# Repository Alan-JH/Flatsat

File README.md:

# Flatsat
Plug and play flatsat testing board for PC104 stack boards

## mainboard
Custom designed main board, includes spaces for three PC104 boards and a passthrough in and passthrough out connector

5V, 3.3V, BATV, GND traces are widened to 0.762mm

## pc104-breakout
Breakout board for probing pc104 pins

## pc104-bridge
Bridge to connect between mainboards

pc104-breakout and pc104-bridge taken and adapted to kicad from https://github.com/JonisK/FlatSat

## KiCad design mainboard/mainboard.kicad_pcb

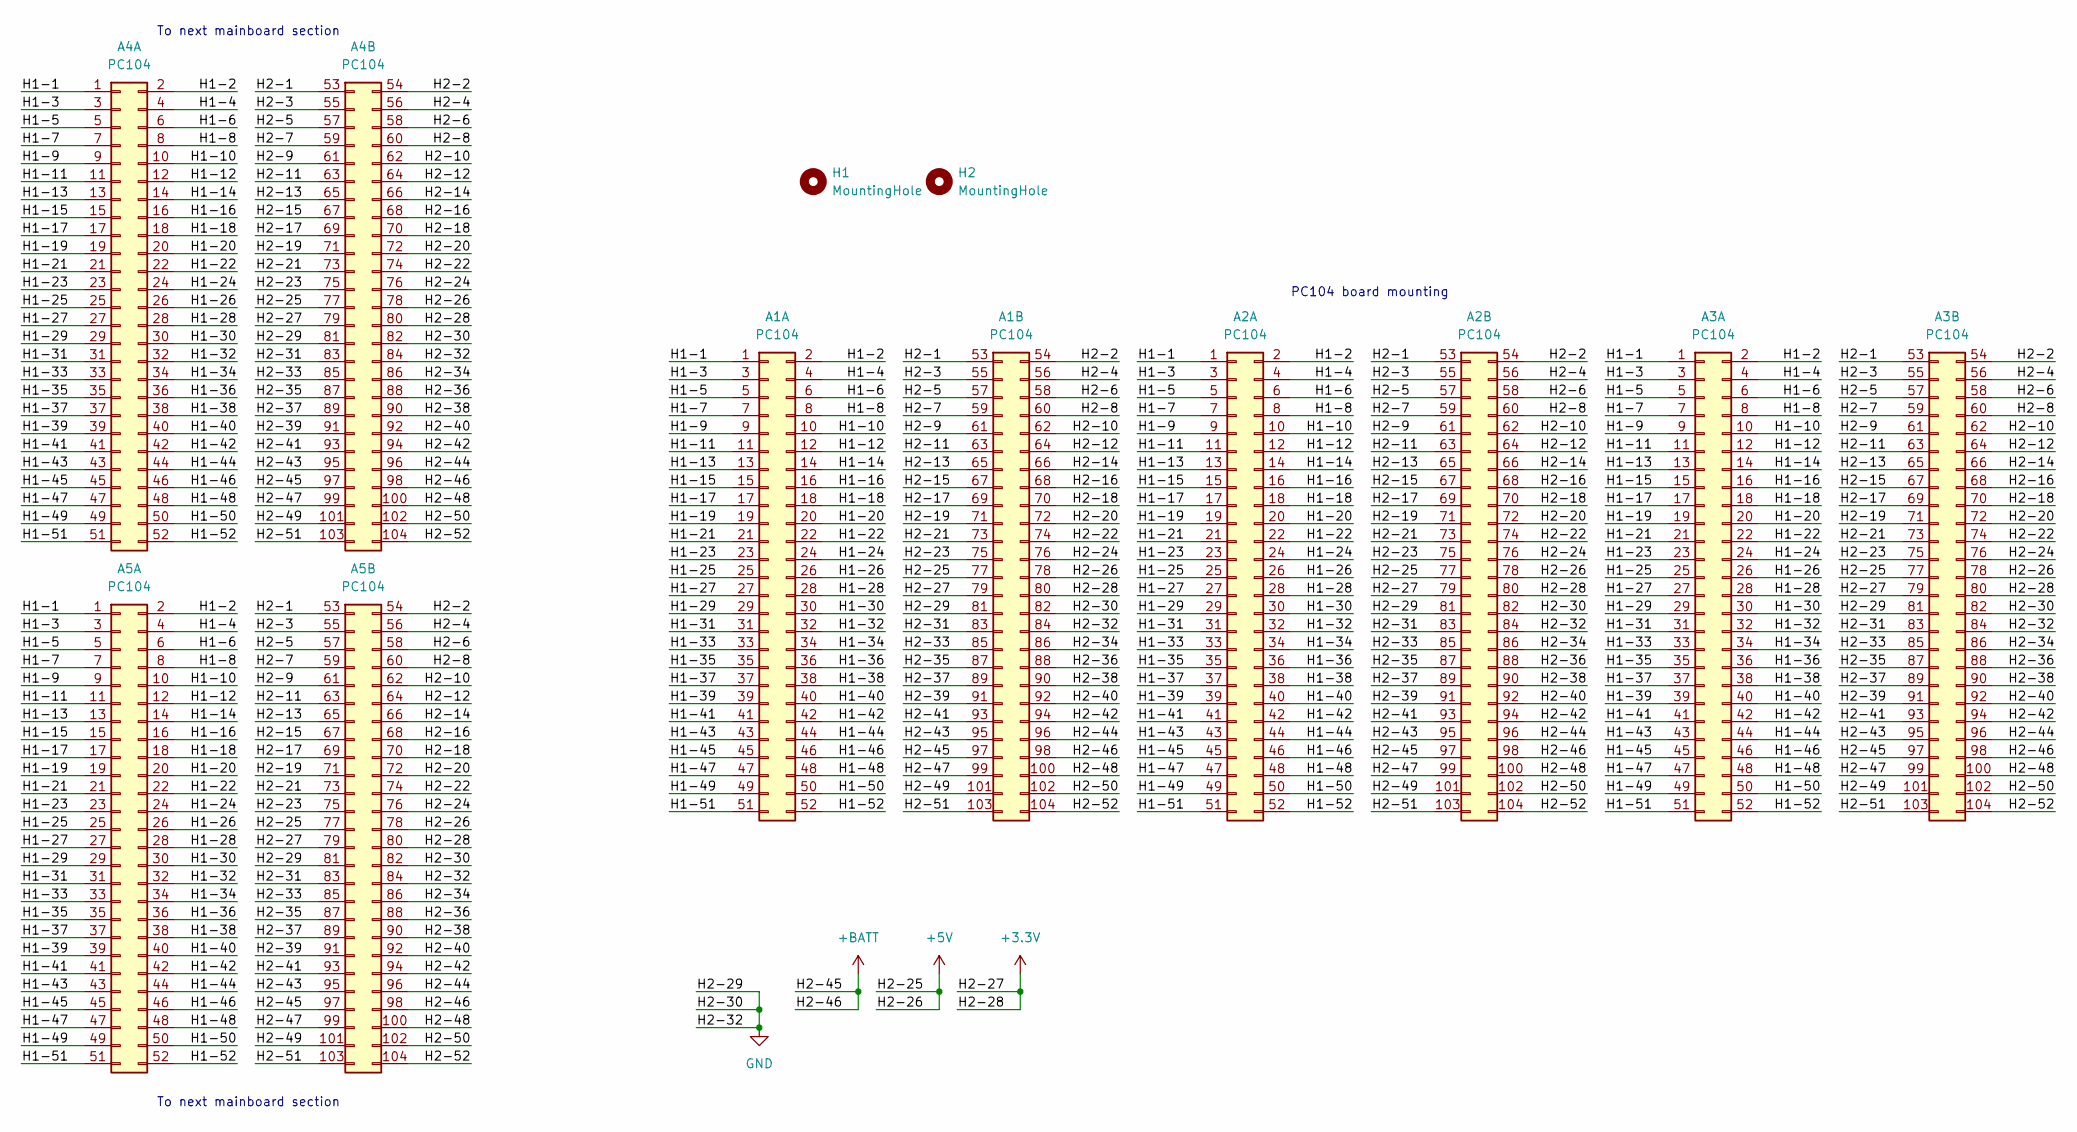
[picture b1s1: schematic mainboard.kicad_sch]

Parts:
A1, A2, A3: PC104
A4, A5: PC104; Header
H1, H2: MountingHole; MountingHole_3.2mm_M3

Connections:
+3V3: A1.79 (Pin_27), A1.80 (Pin_28), A2.79 (Pin_27), A2.80 (Pin_28), A3.79 (Pin_27), A3.80 (Pin_28), A4.79 (Pin_27), A4.80 (Pin_28), A5.79 (Pin_27), A5.80 (Pin_28)
+5V: A1.77 (Pin_25), A1.78 (Pin_26), A2.77 (Pin_25), A2.78 (Pin_26), A3.77 (Pin_25), A3.78 (Pin_26), A4.77 (Pin_25), A4.78 (Pin_26), A5.77 (Pin_25), A5.78 (Pin_26)
+BATT: A1.97 (Pin_45), A1.98 (Pin_46), A2.97 (Pin_45), A2.98 (Pin_46), A3.97 (Pin_45), A3.98 (Pin_46), A4.97 (Pin_45), A4.98 (Pin_46), A5.97 (Pin_45), A5.98 (Pin_46)
/H1-1: A1.1, A2.1, A3.1, A4.1, A5.1
/H1-2: A1.2, A2.2, A3.2, A4.2, A5.2
/H1-3: A1.3, A2.3, A3.3, A4.3, A5.3
/H1-4: A1.4, A2.4, A3.4, A4.4, A5.4
/H1-5: A1.5, A2.5, A3.5, A4.5, A5.5
/H1-6: A1.6, A2.6, A3.6, A4.6, A5.6
/H1-7: A1.7, A2.7, A3.7, A4.7, A5.7
/H1-8: A1.8, A2.8, A3.8, A4.8, A5.8
/H1-9: A1.9, A2.9, A3.9, A4.9, A5.9
/H1-10: A1.10, A2.10, A3.10, A4.10, A5.10
/H1-11: A1.11, A2.11, A3.11, A4.11, A5.11
/H1-12: A1.12, A2.12, A3.12, A4.12, A5.12
/H1-13: A1.13, A2.13, A3.13, A4.13, A5.13
/H1-14: A1.14, A2.14, A3.14, A4.14, A5.14
/H1-15: A1.15, A2.15, A3.15, A4.15, A5.15
/H1-16: A1.16, A2.16, A3.16, A4.16, A5.16
/H1-17: A1.17, A2.17, A3.17, A4.17, A5.17
/H1-18: A1.18, A2.18, A3.18, A4.18, A5.18
/H1-19: A1.19, A2.19, A3.19, A4.19, A5.19
/H1-20: A1.20, A2.20, A3.20, A4.20, A5.20
/H1-21: A1.21, A2.21, A3.21, A4.21, A5.21
/H1-22: A1.22, A2.22, A3.22, A4.22, A5.22
/H1-23: A1.23, A2.23, A3.23, A4.23, A5.23
/H1-24: A1.24, A2.24, A3.24, A4.24, A5.24
/H1-25: A1.25, A2.25, A3.25, A4.25, A5.25
/H1-26: A1.26, A2.26, A3.26, A4.26, A5.26
/H1-27: A1.27, A2.27, A3.27, A4.27, A5.27
/H1-28: A1.28, A2.28, A3.28, A4.28, A5.28
/H1-29: A1.29, A2.29, A3.29, A4.29, A5.29
/H1-30: A1.30, A2.30, A3.30, A4.30, A5.30
/H1-31: A1.31, A2.31, A3.31, A4.31, A5.31
/H1-32: A1.32, A2.32, A3.32, A4.32, A5.32
/H1-33: A1.33, A2.33, A3.33, A4.33, A5.33
/H1-34: A1.34, A2.34, A3.34, A4.34, A5.34
/H1-35: A1.35, A2.35, A3.35, A4.35, A5.35
/H1-36: A1.36, A2.36, A3.36, A4.36, A5.36
/H1-37: A1.37, A2.37, A3.37, A4.37, A5.37
/H1-38: A1.38, A2.38, A3.38, A4.38, A5.38
/H1-39: A1.39, A2.39, A3.39, A4.39, A5.39
/H1-40: A1.40, A2.40, A3.40, A4.40, A5.40
/H1-41: A1.41, A2.41, A3.41, A4.41, A5.41
/H1-42: A1.42, A2.42, A3.42, A4.42, A5.42
/H1-43: A1.43, A2.43, A3.43, A4.43, A5.43
/H1-44: A1.44, A2.44, A3.44, A4.44, A5.44
/H1-45: A1.45, A2.45, A3.45, A4.45, A5.45
/H1-46: A1.46, A2.46, A3.46, A4.46, A5.46
/H1-47: A1.47, A2.47, A3.47, A4.47, A5.47
/H1-48: A1.48, A2.48, A3.48, A4.48, A5.48
/H1-49: A1.49, A2.49, A3.49, A4.49, A5.49
/H1-50: A1.50, A2.50, A3.50, A4.50, A5.50
/H1-51: A1.51, A2.51, A3.51, A4.51, A5.51
/H1-52: A1.52, A2.52, A3.52, A4.52, A5.52
/H2-1: A1.53 (Pin_1), A2.53 (Pin_1), A3.53 (Pin_1), A4.53 (Pin_1), A5.53 (Pin_1)
/H2-2: A1.54 (Pin_2), A2.54 (Pin_2), A3.54 (Pin_2), A4.54 (Pin_2), A5.54 (Pin_2)
/H2-3: A1.55 (Pin_3), A2.55 (Pin_3), A3.55 (Pin_3), A4.55 (Pin_3), A5.55 (Pin_3)
/H2-4: A1.56 (Pin_4), A2.56 (Pin_4), A3.56 (Pin_4), A4.56 (Pin_4), A5.56 (Pin_4)
/H2-5: A1.57 (Pin_5), A2.57 (Pin_5), A3.57 (Pin_5), A4.57 (Pin_5), A5.57 (Pin_5)
/H2-6: A1.58 (Pin_6), A2.58 (Pin_6), A3.58 (Pin_6), A4.58 (Pin_6), A5.58 (Pin_6)
/H2-7: A1.59 (Pin_7), A2.59 (Pin_7), A3.59 (Pin_7), A4.59 (Pin_7), A5.59 (Pin_7)
/H2-8: A1.60 (Pin_8), A2.60 (Pin_8), A3.60 (Pin_8), A4.60 (Pin_8), A5.60 (Pin_8)
/H2-9: A1.61 (Pin_9), A2.61 (Pin_9), A3.61 (Pin_9), A4.61 (Pin_9), A5.61 (Pin_9)
/H2-10: A1.62 (Pin_10), A2.62 (Pin_10), A3.62 (Pin_10), A4.62 (Pin_10), A5.62 (Pin_10)
/H2-11: A1.63 (Pin_11), A2.63 (Pin_11), A3.63 (Pin_11), A4.63 (Pin_11), A5.63 (Pin_11)
/H2-12: A1.64 (Pin_12), A2.64 (Pin_12), A3.64 (Pin_12), A4.64 (Pin_12), A5.64 (Pin_12)
/H2-13: A1.65 (Pin_13), A2.65 (Pin_13), A3.65 (Pin_13), A4.65 (Pin_13), A5.65 (Pin_13)
/H2-14: A1.66 (Pin_14), A2.66 (Pin_14), A3.66 (Pin_14), A4.66 (Pin_14), A5.66 (Pin_14)
/H2-15: A1.67 (Pin_15), A2.67 (Pin_15), A3.67 (Pin_15), A4.67 (Pin_15), A5.67 (Pin_15)
/H2-16: A1.68 (Pin_16), A2.68 (Pin_16), A3.68 (Pin_16), A4.68 (Pin_16), A5.68 (Pin_16)
/H2-17: A1.69 (Pin_17), A2.69 (Pin_17), A3.69 (Pin_17), A4.69 (Pin_17), A5.69 (Pin_17)
/H2-18: A1.70 (Pin_18), A2.70 (Pin_18), A3.70 (Pin_18), A4.70 (Pin_18), A5.70 (Pin_18)
/H2-19: A1.71 (Pin_19), A2.71 (Pin_19), A3.71 (Pin_19), A4.71 (Pin_19), A5.71 (Pin_19)
/H2-20: A1.72 (Pin_20), A2.72 (Pin_20), A3.72 (Pin_20), A4.72 (Pin_20), A5.72 (Pin_20)
/H2-21: A1.73 (Pin_21), A2.73 (Pin_21), A3.73 (Pin_21), A4.73 (Pin_21), A5.73 (Pin_21)
/H2-22: A1.74 (Pin_22), A2.74 (Pin_22), A3.74 (Pin_22), A4.74 (Pin_22), A5.74 (Pin_22)
/H2-23: A1.75 (Pin_23), A2.75 (Pin_23), A3.75 (Pin_23), A4.75 (Pin_23), A5.75 (Pin_23)
/H2-24: A1.76 (Pin_24), A2.76 (Pin_24), A3.76 (Pin_24), A4.76 (Pin_24), A5.76 (Pin_24)
/H2-31: A1.83 (Pin_31), A2.83 (Pin_31), A3.83 (Pin_31), A4.83 (Pin_31), A5.83 (Pin_31)
/H2-33: A1.85 (Pin_33), A2.85 (Pin_33), A3.85 (Pin_33), A4.85 (Pin_33), A5.85 (Pin_33)
/H2-34: A1.86 (Pin_34), A2.86 (Pin_34), A3.86 (Pin_34), A4.86 (Pin_34), A5.86 (Pin_34)
/H2-35: A1.87 (Pin_35), A2.87 (Pin_35), A3.87 (Pin_35), A4.87 (Pin_35), A5.87 (Pin_35)
/H2-36: A1.88 (Pin_36), A2.88 (Pin_36), A3.88 (Pin_36), A4.88 (Pin_36), A5.88 (Pin_36)
/H2-37: A1.89 (Pin_37), A2.89 (Pin_37), A3.89 (Pin_37), A4.89 (Pin_37), A5.89 (Pin_37)
/H2-38: A1.90 (Pin_38), A2.90 (Pin_38), A3.90 (Pin_38), A4.90 (Pin_38), A5.90 (Pin_38)
/H2-39: A1.91 (Pin_39), A2.91 (Pin_39), A3.91 (Pin_39), A4.91 (Pin_39), A5.91 (Pin_39)
/H2-40: A1.92 (Pin_40), A2.92 (Pin_40), A3.92 (Pin_40), A4.92 (Pin_40), A5.92 (Pin_40)
/H2-41: A1.93 (Pin_41), A2.93 (Pin_41), A3.93 (Pin_41), A4.93 (Pin_41), A5.93 (Pin_41)
/H2-42: A1.94 (Pin_42), A2.94 (Pin_42), A3.94 (Pin_42), A4.94 (Pin_42), A5.94 (Pin_42)
/H2-43: A1.95 (Pin_43), A2.95 (Pin_43), A3.95 (Pin_43), A4.95 (Pin_43), A5.95 (Pin_43)
/H2-44: A1.96 (Pin_44), A2.96 (Pin_44), A3.96 (Pin_44), A4.96 (Pin_44), A5.96 (Pin_44)
/H2-47: A1.99 (Pin_47), A2.99 (Pin_47), A3.99 (Pin_47), A4.99 (Pin_47), A5.99 (Pin_47)
/H2-48: A1.100 (Pin_48), A2.100 (Pin_48), A3.100 (Pin_48), A4.100 (Pin_48), A5.100 (Pin_48)
/H2-49: A1.101 (Pin_49), A2.101 (Pin_49), A3.101 (Pin_49), A4.101 (Pin_49), A5.101 (Pin_49)
/H2-50: A1.102 (Pin_50), A2.102 (Pin_50), A3.102 (Pin_50), A4.102 (Pin_50), A5.102 (Pin_50)
/H2-51: A1.103 (Pin_51), A2.103 (Pin_51), A3.103 (Pin_51), A4.103 (Pin_51), A5.103 (Pin_51)
/H2-52: A1.104 (Pin_52), A2.104 (Pin_52), A3.104 (Pin_52), A4.104 (Pin_52), A5.104 (Pin_52)
GND: A1.81 (Pin_29), A1.82 (Pin_30), A1.84 (Pin_32), A2.81 (Pin_29), A2.82 (Pin_30), A2.84 (Pin_32), A3.81 (Pin_29), A3.82 (Pin_30), A3.84 (Pin_32), A4.81 (Pin_29), A4.82 (Pin_30), A4.84 (Pin_32), A5.81 (Pin_29), A5.82 (Pin_30), A5.84 (Pin_32)

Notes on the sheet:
PC104 board mounting
To next mainboard section

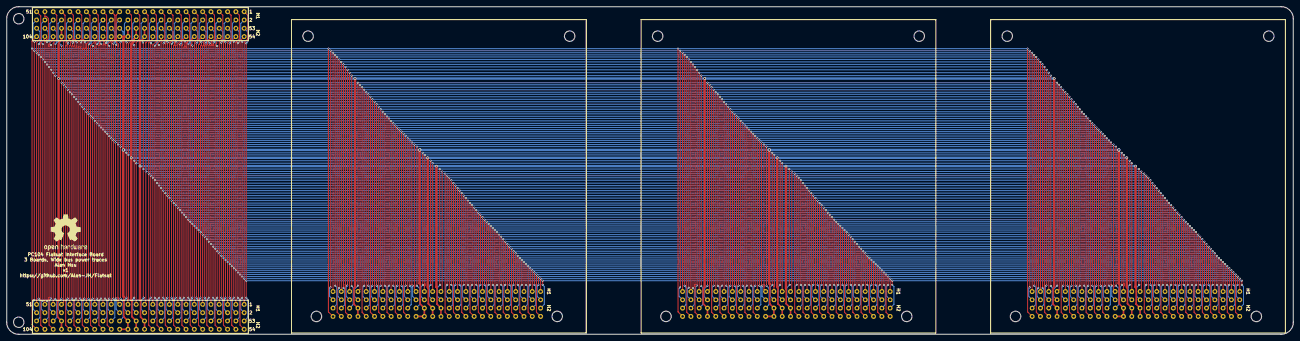
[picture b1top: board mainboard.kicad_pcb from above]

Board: 2 copper layers, 393.6 x 100.2 mm, 7 parts (0 on the bottom side), 99 nets.

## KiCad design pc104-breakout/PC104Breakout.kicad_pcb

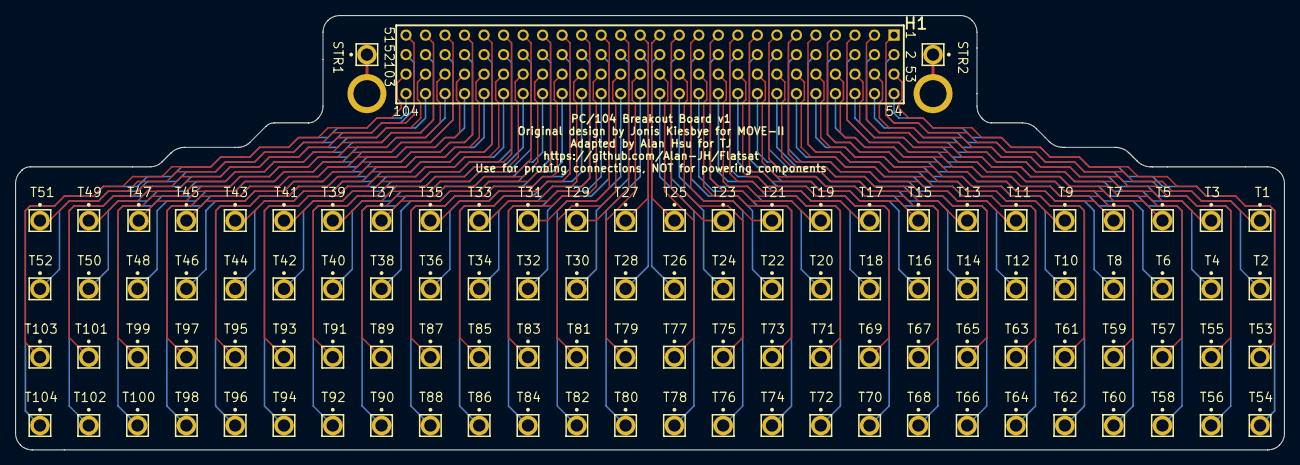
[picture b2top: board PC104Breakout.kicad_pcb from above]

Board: 2 copper layers, 165.1 x 56.5 mm, 107 parts (0 on the bottom side), 105 nets.

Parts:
H1: MOVE-II PC104; PC104
STR1, STR2: Testpoint; PIN1
T1, T2, T3, T4, T5, T6, T7, T8, T9, T10, T11, T12, T13, T14, T15, T16, T17, T18, T19, T20, T21, T22, T23, T24, T25, T26, T27, T28, T29, T30, T31, T32, T33, T34, T35, T36, T37, T38, T39, T40, T41, T42, T43, T44, T45, T46, T47, T48, T49, T50, T51, T52, T53, T54, T55, T56, T57, T58, T59, T60, T61, T62, T63, T64, T65, T66, T67, T68, T69, T70, T71, T72, T73, T74, T75, T76, T77, T78, T79, T80, T81, T82, T83, T84, T85, T86, T87, T88, T89, T90, T91, T92, T93, T94, T95, T96, T97, T98, T99, T100, T101, T102, T103, T104: Testpoint; PIN1

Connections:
CHASSIS: STR1.1, STR2.1
TRACE1: H1.1, T1.1
TRACE2: H1.2, T2.1
TRACE3: H1.3, T3.1
TRACE4: H1.4, T4.1
TRACE5: H1.5, T5.1
TRACE6: H1.6, T6.1
TRACE7: H1.7, T7.1
TRACE8: H1.8, T8.1
TRACE9: H1.9, T9.1
TRACE10: H1.10, T10.1
TRACE11: H1.11, T11.1
TRACE12: H1.12, T12.1
TRACE13: H1.13, T13.1
TRACE14: H1.14, T14.1
TRACE15: H1.15, T15.1
TRACE16: H1.16, T16.1
TRACE17: H1.17, T17.1
TRACE18: H1.18, T18.1
TRACE19: H1.19, T19.1
TRACE20: H1.20, T20.1
TRACE21: H1.21, T21.1
TRACE22: H1.22, T22.1
TRACE23: H1.23, T23.1
TRACE24: H1.24, T24.1
TRACE25: H1.25, T25.1
TRACE26: H1.26, T26.1
TRACE27: H1.27, T27.1
TRACE28: H1.28, T28.1
TRACE29: H1.29, T29.1
TRACE30: H1.30, T30.1
TRACE31: H1.31, T31.1
TRACE32: H1.32, T32.1
TRACE33: H1.33, T33.1
TRACE34: H1.34, T34.1
TRACE35: H1.35, T35.1
TRACE36: H1.36, T36.1
TRACE37: H1.37, T37.1
TRACE38: H1.38, T38.1
TRACE39: H1.39, T39.1
TRACE40: H1.40, T40.1
TRACE41: H1.41, T41.1
TRACE42: H1.42, T42.1
TRACE43: H1.43, T43.1
TRACE44: H1.44, T44.1
TRACE45: H1.45, T45.1
TRACE46: H1.46, T46.1
TRACE47: H1.47, T47.1
TRACE48: H1.48, T48.1
TRACE49: H1.49, T49.1
TRACE50: H1.50, T50.1
TRACE51: H1.51, T51.1
TRACE52: H1.52, T52.1
TRACE53: H1.53, T53.1
TRACE54: H1.54, T54.1
TRACE55: H1.55, T55.1
TRACE56: H1.56, T56.1
TRACE57: H1.57, T57.1
TRACE58: H1.58, T58.1
TRACE59: H1.59, T59.1
TRACE60: H1.60, T60.1
TRACE61: H1.61, T61.1
TRACE62: H1.62, T62.1
TRACE63: H1.63, T63.1
TRACE64: H1.64, T64.1
TRACE65: H1.65, T65.1
TRACE66: H1.66, T66.1
TRACE67: H1.67, T67.1
TRACE68: H1.68, T68.1
TRACE69: H1.69, T69.1
TRACE70: H1.70, T70.1
TRACE71: H1.71, T71.1
TRACE72: H1.72, T72.1
TRACE73: H1.73, T73.1
TRACE74: H1.74, T74.1
TRACE75: H1.75, T75.1
TRACE76: H1.76, T76.1
TRACE77: H1.77, T77.1
TRACE78: H1.78, T78.1
TRACE79: H1.79, T79.1
TRACE80: H1.80, T80.1
TRACE81: H1.81, T81.1
TRACE82: H1.82, T82.1
TRACE83: H1.83, T83.1
TRACE84: H1.84, T84.1
TRACE85: H1.85, T85.1
TRACE86: H1.86, T86.1
TRACE87: H1.87, T87.1
TRACE88: H1.88, T88.1
TRACE89: H1.89, T89.1
TRACE90: H1.90, T90.1
TRACE91: H1.91, T91.1
TRACE92: H1.92, T92.1
TRACE93: H1.93, T93.1
TRACE94: H1.94, T94.1
TRACE95: H1.95, T95.1
TRACE96: H1.96, T96.1
TRACE97: H1.97, T97.1
TRACE98: H1.98, T98.1
TRACE99: H1.99, T99.1
TRACE100: H1.100, T100.1
TRACE101: H1.101, T101.1
TRACE102: H1.102, T102.1
TRACE103: H1.103, T103.1
TRACE104: H1.104, T104.1

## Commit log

2022-05-19 init commit
2022-05-20 lay out the PC104 boards
2022-05-20 fix gitignore
2022-05-27 grounding
2022-06-13 bus power flags, finish left side routing
2022-06-13 silkscreen, horizontal routing
2022-06-14 finish pc104 connections
2022-06-14 add bridge and breakout
2022-06-14 adapt bridge and breakout to jlcpcb tolerance, add pin numbers to mainboard
2022-06-14 fix board edge
2022-06-18 make prettier
